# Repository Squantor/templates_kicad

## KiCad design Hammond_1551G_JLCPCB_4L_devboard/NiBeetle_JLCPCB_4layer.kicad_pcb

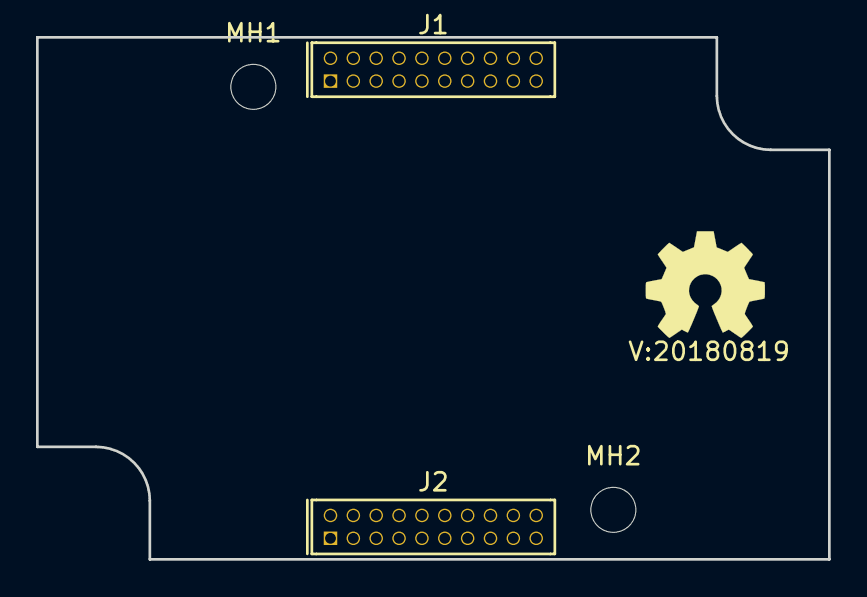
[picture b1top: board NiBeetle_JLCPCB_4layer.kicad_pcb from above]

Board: 4 copper layers, 44.0 x 29.0 mm, 6 parts (0 on the bottom side), 5 nets, no tracks yet.

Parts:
J1: DevBoardDigital; Header-0127-2X10-H006
J2: DevBoardAnalog; Header-0127-2X10-H006
MH1, MH2: MountingHole; MountingHole_2.5mm_no_metal
N1: OHWLOGO; OSHW-Symbol_6.7x6mm_SilkScreen
N2: 20180819; Label_version

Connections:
VCC: J2.1, J2.2
VDD: J1.1, J1.2
VDDA: J2.5, J2.6
VSS: J1.3, J1.4, J2.3, J2.4
VSSA: J2.7, J2.8
